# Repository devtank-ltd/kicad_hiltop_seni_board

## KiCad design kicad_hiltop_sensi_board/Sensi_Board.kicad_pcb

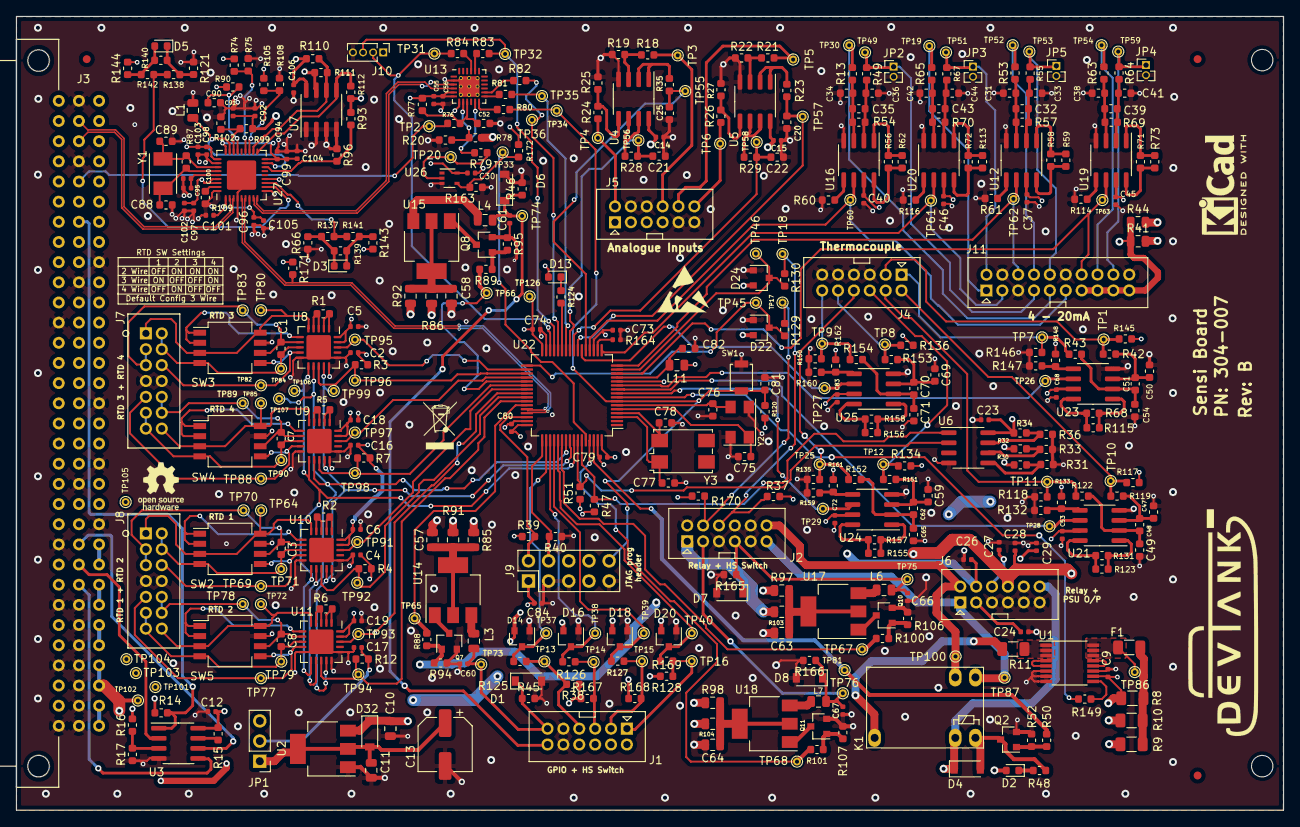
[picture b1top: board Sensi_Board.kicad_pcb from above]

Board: 4 copper layers, 159.6 x 100.0 mm, 451 parts (0 on the bottom side), 240 nets.

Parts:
C1, C3, C7, C8, C20, C21, C22, C25, C32, C35, C39, C43, C48, C51, C52, C62, C70, C81, C82, C90: 100nF; C_0603_1608Metric
C2, C4, C5, C6, C9, C12, C14, C15, C16, C17, C18, C19, C23, C24, C26, C27, C28, C29, C30, C37, C40, C45, C46, C53, C56, C60, C61, C66, C67, C68, C72, C73, C74, C79, C80, C83, C84, C92, C94, C95, C96, C97, C98, C99, C101: 100nF; C_0402_1005Metric
C10, C11: 10uF; C_0805_2012Metric
C13: 100uF; CP_Elec_6.3x7.7
C31, C33, C34, C36, C38, C41, C42, C44: 1uF; C_0603_1608Metric
C47, C49, C50, C54, C59, C65, C69, C71: 1nF; C_0603_1608Metric
C55, C100, C102, C103, C104, C105: 4.7uF; C_0402_1005Metric
C57, C58, C63, C64: DNF; C_0805_2012Metric
C75, C76: 18pF; C_0603_1608Metric
C77, C78: 4.3pF; C_0603_1608Metric
C88, C89: 33pF; C_0603_1608Metric
C91: 1uF; C_0402_1005Metric
C106: DNF; C_0402_1005Metric
D1, D6, D7, D8: D_Schottky; D_SOD-123
D2, D3, D5, D13: GRN; LED_0603_1608Metric
D4: BAT54T1G; D_SOD-123
D14, D16, D18, D20, D22, D24: BAV99; SOT-23
D32: MBR230LSFT1G; D_SOD-123
F1: Polyfuse; R_1206_3216Metric
J1, J2, J4, J5, J6: Conn_02x06_Top_Bottom; Molex2x06
J3: Conn_03x32_DIN41612; Socket_DIN41612-CaseC1-full-Male-96Pin-3rows_correct
J7, J8: Conn_02x07_Top_Bottom; 87831-1420_Molex_Milligrid
J9: Conn_02x05_Odd_Even; PinHeader_2x05_P2.54mm_Vertical
J10: Conn_01x04; PinHeader_1x04_P1.27mm_Vertical
J11: Conn_02x10_Counter_Clockwise; Molex_Milligrid_2x10
JP1: Jumper_NC_Dual; PinHeader_1x03_P2.54mm_Vertical
JP2, JP3, JP4, JP5: Jumper_NC_Small; PinHeader_1x02_P1.27mm_Vertical
K1: HRS1KH-S; Relay_SPDT_HRS1KH-S
L1: 500mA/0.10DCR; L_0805_2012Metric
L3, L4, L6, L7, L11: 2A/0.05DCR; L_0805_2012Metric
Q2, Q7, Q8, Q10, Q11: ZXMN6A07F; SOT-23
R1, R2, R5, R6, R50: 470R; R_0603_1608Metric
R3, R4, R7, R12, R14, R18, R21, R24, R26, R37, R52, R75, R77, R99, R105, R111, R120, R132, R133, R147, R148, R159, R160, R161, R162, R170: 10K; R_0603_1608Metric
R8, R9: DNF; R_1206_3216Metric
R10, R11: 0R; R_1206_3216Metric
R13, R49, R53, R55, R63, R64, R65, R67: 68R; R_0603_1608Metric
R15, R16, R47, R51: 4K7; R_0603_1608Metric
R17, R31, R33, R36, R38, R59, R62, R73, R74, R96, R108, R110, R112, R113, R115, R123, R137, R138, R143, R144, R155, R156, R163, R167, R168, R169, R172: DNF; R_0603_1608Metric
R19, R22, R25, R27: 16K; R_0603_1608Metric
R20: 47K; R_0603_1608Metric
R23, R28, R29, R35: 100R; R_0603_1608Metric
R30, R32, R34, R60, R61, R66, R76, R79, R80, R83, R84, R114, R116, R121, R149: 0R; R_0603_1608Metric
R39, R40, R45, R46, R90, R93, R94, R95, R106, R107, R139, R140, R165, R166: 100K; R_0603_1608Metric
R41, R85, R86, R97, R98: DNF; R_0805_2012Metric
R42, R43, R88, R89, R100, R101, R119, R122, R125, R126, R127, R128, R129, R130, R151, R152, R153, R154: 1K; R_0603_1608Metric
R44, R91, R92, R103, R104: 0R; R_0805_2012Metric
R48: 2K2; R_0603_1608Metric
R54, R57, R69, R70: 30R; R_0603_1608Metric
R56, R58, R71, R72: 12.4K; R_0603_1608Metric
R68, R131, R157, R158: 1.58K; R_0603_1608Metric
R78: 24K; R_0603_1608Metric
R81, R82, R124, R141, R142: 330R; R_0603_1608Metric
R87: 1M; R_0603_1608Metric
R102: 20K; R_0603_1608Metric
R109: 12.0K; R_0603_1608Metric
R117, R118, R134, R135, R136, R145, R146, R150: 10M; R_0603_1608Metric
R164: DNF; R_0402_1005Metric
R171: 1k5; R_0603_1608Metric
SW1: SW_Push; SW_SPST_B3U-1000P
SW2, SW3, SW4, SW5: SW_DIP_x04; SW_DIP_SPSTx04_Slide_Copal_CHS-04B_W7.62mm_P1.27mm
TP1, TP2, TP3, TP4, TP5, TP6, TP7, TP8, TP9, TP10, TP11, TP12, TP13, TP14, TP15, TP16, TP17, TP18, TP19, TP20, TP25, TP26, TP27, TP28, TP29, TP30, TP31, TP32, TP33, TP34, TP35, TP36, TP37, TP38, TP39, TP40, TP45, TP46, TP49, TP51, TP52, TP53, TP54, TP55, TP56, TP57, TP58, TP59, TP60, TP61, TP62, TP63, TP64, TP65, TP66, TP67, TP68, TP69, TP70, TP71, TP72, TP73, TP74, TP75, TP76, TP77, TP78, TP79, TP80, TP81, TP82, TP83, TP84, TP85, TP86, TP87, TP88, TP89, TP90, TP91, TP92, TP93, TP94, TP95, TP96, TP97, TP98, TP99, TP100, TP101, TP102, TP103, TP104, TP105, TP106, TP107, TP126: Test_Point; TestPoint_THTPad_D1.0mm_Drill0.5mm
U1: INA250A4; TSSOP-16_4.4x5mm_P0.65mm
U2: LD1117S33TR_SOT223; SOT-223-3_TabPin2
U3: AT25DN512CSSHF-B; SOIC-8_3.9x4.9mm_P1.27mm
U4, U5: AD8646; SOIC-8_3.9x4.9mm_P1.27mm
U6: LM75B; SOIC-8_3.9x4.9mm_P1.27mm
U7: DNF; SOIC-8_3.9x4.9mm_P1.27mm
U8, U9, U10, U11: MAX31865; TQFN-20-1EP_5x5mm_P0.65mm_EP3.1x3.1mm
U12, U16, U19, U20, U21, U23, U24, U25: MAX4194; SOIC-8_3.9x4.9mm_P1.27mm
U13: CP2102N-A01-GQFN24; CP2102_QFN-24-1EP_4x4mm_P0.5mm_EP2.6x2.6mm_ThermalVias_0.3m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
U14, U15, U17, U18: BTS4140N; SOT-223
U22: STM32F072RBTx; LQFP-64_10x10mm_P0.5mm
U26: M74VHC1GT14DFT2G; SOT-353_SC-70-5
U27: USB2502; QFN-36-1EP_6x6mm_P0.5mm_EP3.7x3.7mm
Y1: 50ppm 24.000MHZ; Crystal_SMD_TXC_7A-2Pin_5x3.2mm
Y2: 8MHZ; Crystal_SMD_Abracon_ABM3C-4Pin_5.0x3.2mm
Y3: ABS25-32.768KHZ-6-T; Crystal_SMD_7050-4Pin_7.0x5.0mm

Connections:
+3V3: C2.1, C4.1, C5.1, C6.1, C9.1, C12.2, C16.1, C17.1, C18.1, C19.1, C23.1, C27.1, C30.2, C37.2, C40.2, C45.2, C46.2, C53.2, C55.1, C56.1, C68.2, C72.2, C73.1, C74.1, C79.1, C80.1, C83.2, C84.2, C96.1, C97.1, C98.1, C101.1, C102.1, C103.1, C105.1, C106.1, D13.2, D14.2, D16.2, D18.2, D20.2, D22.2, D24.2, J6.9, J9.1, J10.1, JP1.2, L11.1, R3.1, R4.1, R7.1, R8.2, R12.1, R14.2, R15.2, R16.2, R30.1, R32.1, R34.1, R37.1, R38.1, R39.1, R47.1, R51.1, R74.1, R77.2, R90.1, R93.1, R105.2, R110.2, R112.1, R117.1, R120.1, R133.2, R134.1, R136.1, R143.2, R144.2, R145.1, R148.2, R161.2, R162.2, R167.1, R168.1, R169.1, R170.1, R171.1, R172.1, TP126.1, U1.10, U3.8, U6.8, U7.8, U8.19, U8.20, U9.19, U9.20, U10.19, U10.20, U11.19, U11.20, U12.7, U13.5, U13.6, U13.7, U16.7, U19.7, U20.7, U21.7, U22.19, U22.32, U22.48, U22.64, U23.7, U24.7, U25.7, U26.5, U27.1, U27.7, U27.13, U27.28, U27.33, U27.34
+3V3_BP: J3.7c, J3.8c, JP1.3, TP104.1
+3V3_LOC: C11.2, C13.1, D32.2, JP1.1, U2.2
+5V: C10.2, C14.2, C15.2, C29.1, C91.1, C92.1, D2.2, D4.1, D32.1, J3.3c, J3.4c, J5.1, J5.2, J5.3, J5.4, J6.12, K1.5, R78.2, R99.1, TP102.1, U2.3, U4.8, U5.8
+12V: C28.1, J3.1c, J3.2c, J6.10, R10.2, R41.2, R85.1, R86.1, R97.1, R98.1, TP101.1
-5V: C26.1, J3.5c, J3.6c, J6.8, TP103.1
/AIN_BUF_CH1: C25.2, R35.1, TP55.1, U22.21
/AIN_BUF_CH2: C21.2, R28.1, TP56.1, U22.25
/AIN_BUF_CH3: C20.2, R23.1, TP57.1, U22.23
/AIN_BUF_CH4: C22.2, R29.1, TP58.1, U22.24
/AIN_CH1: J5.10, R18.2, TP3.1
/AIN_CH2: J5.7, R24.2, TP4.1
/AIN_CH3: J5.11, R21.2, TP5.1
/AIN_CH4: J5.12, R26.2, TP6.1
/F1+: J11.5, R13.2, TP30.1
/F1-: J11.4, JP2.1, R49.2, TP49.1
/F1_OUT: J11.6, TP60.1, U16.6, U22.20
/F2+: J11.1, R65.2, TP19.1
/F2-: J11.11, JP3.1, R67.2, TP51.1
/F2_OUT: J11.2, TP61.1, U20.6, U22.17
/F3+: J11.14, R53.2, TP52.1
/F3-: J11.15, JP5.1, R55.2, TP53.1
/F3_OUT: J11.13, TP62.1, U12.6, U22.16
/F4+: J11.18, R63.2, TP54.1
/F4-: J11.19, JP4.1, R64.2, TP59.1
/F4_OUT: J11.17, TP63.1, U19.6, U22.14
/F_Vs: J11.7, J11.8, J11.9, J11.10, R41.1, R44.1
/GPIO1: D14.3, R125.1, TP37.1, U22.50
/GPIO1_EXT: J1.4, R38.2, R125.2, TP13.1
/GPIO2: D16.3, R126.1, TP38.1, U22.51
/GPIO2_EXT: J1.3, R126.2, R167.2, TP14.1
/GPIO3: D18.3, R127.1, TP39.1, U22.52
/GPIO3_EXT: J1.2, R127.2, R168.2, TP15.1
/GPIO4: D20.3, R128.1, TP40.1, U22.53
/GPIO4_EXT: J1.1, R128.2, R169.2, TP16.1
/GPIO5: D22.3, R129.1, TP45.1, U22.33
/GPIO5_EXT: J2.8, R129.2, R170.2, TP17.1
/GPIO6: D24.3, R130.1, TP46.1, U22.15
/GPIO6_EXT: J2.9, R37.2, R130.2, TP18.1
/HS_CTRL_SW1: R88.2, TP65.1, U22.43
/HS_CTRL_SW2: R89.2, TP66.1, U22.37
/HS_CTRL_SW3: R100.2, TP67.1, U22.54
/HS_CTRL_SW4: R101.2, TP68.1, U22.61
/HS_OUT1: C60.1, D1.1, J1.6, L3.1, R45.1, TP73.1
/HS_OUT2: C61.1, D6.1, J1.12, L4.1, R46.1, TP74.1
/HS_OUT3: C66.1, D7.1, J2.4, L6.1, R165.1, TP75.1
/HS_OUT4: C67.1, D8.1, J2.2, L7.1, R166.1, TP76.1
/I_MON: R149.2, U1.9
/OUT1_COM: K1.2, R11.1
/OUT1_NC: J2.6, J6.1, K1.4, TP87.1
/OUT1_NO: J2.12, J6.7, K1.3, TP100.1
/PORT_SEL: J3.26b, R14.1, U3.1
/RESET: J3.28b, R76.2, TP2.1
/RL1_OUT: R50.2, TP81.1, U22.62
/RTD1_CS: R4.2, TP92.1, U10.13, U22.41
/RTD1_F+: J8.1, SW2.3, SW2.8, TP64.1, U10.5
/RTD1_F-: J8.10, SW2.5, TP69.1, U10.9
/RTD1_INT: TP91.1, U10.18, U22.39
/RTD1_R+: C3.2, J8.2, J8.3, SW2.6, TP70.1, U10.7
/RTD1_R-: C3.1, J8.8, J8.9, SW2.4, TP71.1, U10.8
/RTD2_CS: R12.2, TP94.1, U11.13, U22.42
/RTD2_F+: J8.14, SW5.3, SW5.8, TP72.1, U11.5
/RTD2_F-: J8.5, SW5.5, TP77.1, U11.9
/RTD2_INT: TP93.1, U11.18, U22.40
/RTD2_R+: C8.2, J8.12, J8.13, SW5.6, TP78.1, U11.7
/RTD2_R-: C8.1, J8.6, J8.7, SW5.4, TP79.1, U11.8
/RTD3_CS: R3.2, TP96.1, U8.13, U22.35
/RTD3_F+: J7.1, SW3.3, SW3.8, TP80.1, U8.5
/RTD3_F-: J7.10, SW3.5, TP82.1, U8.9
/RTD3_INT: TP95.1, U8.18, U22.34
/RTD3_R+: C1.2, J7.2, J7.3, SW3.6, TP83.1, U8.7
/RTD3_R-: C1.1, J7.8, J7.9, SW3.4, TP84.1, U8.8
/RTD4_CS: R7.2, TP98.1, U9.13, U22.38
/RTD4_F+: J7.14, SW4.3, SW4.8, TP85.1, U9.5
/RTD4_F-: J7.5, SW4.5, TP88.1, U9.9
/RTD4_INT: TP97.1, U9.18, U22.36
/RTD4_R+: C7.2, J7.12, J7.13, SW4.6, TP89.1, U9.7
/RTD4_R-: C7.1, J7.6, J7.7, SW4.4, TP90.1, U9.8
/SPI0_CLK: J3.10b, U3.6
/SPI0_MISO: J3.9b, U3.2
/SPI0_MOSI: J3.8b, U3.5
/STM_BOOT0_OUT: R163.1, R172.2, TP33.1, U22.60, U26.4
/STM_DEBUG_RX: J10.2, R84.1, TP31.1, U22.30
/STM_DEBUG_TX: J10.3, R83.1, TP32.1, U22.29
/STM_Micro/ADC8: R149.1, U22.8
/STM_RES1: R81.1, TP35.1, U22.26
/STM_RES2: R82.1, TP36.1, U22.28
/STM_RESET: C81.1, J9.10, R80.1, R120.2, SW1.2, TP34.1, U22.7
/STM_SCL: R51.2, U6.2, U22.58
/STM_SDA: R47.2, U6.1, U22.59
/STM_SPI1_MISO: TP99.1, U8.14, U9.14, U10.14, U11.14, U22.56
/STM_SPI1_MOSI: TP106.1, U8.11, U9.11, U10.11, U11.11, U22.57
/STM_SPI1_SCK: TP107.1, U8.12, U9.12, U10.12, U11.12, U22.55
/STM_USB_DATA_N: U22.44, U27.5
/STM_USB_DATA_P: R171.2, U22.45, U27.6
/SWD_IO: J9.2, R39.2, U22.46
/SWD_SCK: J9.4, R40.2, U22.49
/TH1+: J4.2, R42.2, R145.2, TP1.1
/TH1-: J4.1, R43.2, R146.1, TP7.1
/TH1_OUT: TP26.1, U22.11, U23.6
/TH2+: J4.11, R136.2, R153.2, TP8.1
/TH2-: J4.12, R150.1, R154.2, TP9.1
/TH2_OUT: TP27.1, U22.22, U25.6
/TH3+: J4.7, R117.2, R119.2, TP10.1
/TH3-: J4.8, R118.1, R122.2, TP11.1
/TH3_OUT: TP28.1, U21.6, U22.10
/TH4+: J4.9, R134.2, R151.2, TP12.1
/TH4-: J4.10, R135.1, R152.2, TP25.1
/TH4_OUT: TP29.1, U22.9, U24.6
/USB_DATA_N: J3.30b, U27.3
/USB_DATA_P: J3.31b, U27.2
/USB_DEBUG_N: U13.4, U27.9
/USB_DEBUG_P: U13.3, U27.8
ADJ_DC: C24.1, J2.1, J3.9c, J3.10c, J6.2, R9.2, R44.2, R91.1, R92.1, R103.1, R104.1, TP105.1
GND: C2.2, C4.2, C5.2, C6.2, C9.2, C10.1, C11.1, C12.1, C13.2, C14.1, C15.1, C16.2, C17.2, C18.2, C19.2, C20.1, C21.1, C22.1, C23.2, C24.2, C25.1, C26.2, C27.2, C28.2, C29.2, C30.1, C31.1, C33.2, C34.1, C36.2, C37.1, C38.1, C40.1, C41.2, C42.1, C44.2, C45.1, C46.1, C47.1, C49.2, C50.1, C52.2, C53.1, C54.2, C55.2, C56.2, C57.2, C58.2, C59.1, C60.2, C61.2, C63.2, C64.2, C65.2, C66.2, C67.2, C68.1, C69.1, C71.2, C72.1, C73.2, C74.2, C75.2, C76.2, C77.2, C78.2, C79.2, C80.2, C81.2, C82.2, C83.1, C84.1, C88.2, C89.1, C90.2, C91.2, C92.2, C94.2, C95.2, C96.2, C97.2, C98.2, C99.2, C100.2, C101.2, C102.2, C103.2, C104.2, C105.2, C106.2, D1.2, D6.2, D7.2, D8.2, D14.1, D16.1, D18.1, D20.1, D22.1, D24.1, J1.5, J1.11, J2.3, J2.5, J2.7, J2.10, J2.11, J3.1a, J3.1b, J3.2b, J3.3b, J3.4a, J3.4b, J3.5b, J3.6b, J3.7a, J3.7b, J3.10a, J3.11c, J3.13b, J3.14c, J3.17c, J3.21a, J3.23b, J3.24c, J3.29b, J3.32b, J4.3, J4.4, J4.5, J4.6, J5.5, J5.6, J5.8, J5.9, J6.3, J6.4, J6.5, J6.6, J6.11, J7.4, J7.11, J8.4, J8.11, J9.3, J9.5, J9.9, J10.4, J11.3, J11.12, J11.16, J11.20, JP2.2, JP3.2, JP4.2, JP5.2, L1.1, Q2.2, Q7.2, Q8.2, Q10.2, Q11.2, R17.1, R19.1, R20.1, R22.1, R25.1, R27.1, R31.2, R33.2, R36.2, R40.1, R45.2, R46.2, R52.1, R60.2, R61.2, R66.1, R75.1, R94.1, R95.1, R96.1, R102.2, R106.1, R107.1, R108.2, R109.2, R111.2, R114.2, R116.2, R118.2, R121.1, R132.2, R135.2, R146.2, R147.2, R150.2, R159.2, R160.2, R163.2, R164.2, R165.2, R166.2, SW1.1, SW2.7, SW3.7, SW4.7, SW5.7, U1.6, U1.7, U1.8, U1.11, U2.1, U3.4, U4.4, U5.4, U6.4, U7.1, U7.2, U7.3, U7.4, U7.7, U8.10, U8.15, U8.16, U8.21, U9.10, U9.15, U9.16, U9.21, U10.10, U10.15, U10.16, U10.21, U11.10, U11.15, U11.16, U11.21, U12.4, U13.2, U13.25, U16.4, U19.4, U20.4, U21.4, U22.12, U22.31, U22.47, U22.63, U23.4, U24.4, U25.4, U26.3, U27.4, U27.10, U27.29, U27.36, U27.37, Y2.2, Y2.4
unnamed: C31.2, C32.1, R53.1, R57.1, U12.3
unnamed: C32.2, C33.1, R55.1, R57.2, U12.2
unnamed: C34.2, C35.1, R13.1, R54.1, U16.3
unnamed: C35.2, C36.1, R49.1, R54.2, U16.2
unnamed: C38.2, C39.1, R63.1, R69.1, U19.3
unnamed: C39.2, C41.1, R64.1, R69.2, U19.2
unnamed: C42.2, C43.1, R65.1, R70.1, U20.3
unnamed: C43.2, C44.1, R67.1, R70.2, U20.2
unnamed: C47.2, C48.1, R119.1, U21.3
unnamed: C48.2, C49.1, R122.1, U21.2
unnamed: C50.2, C51.1, R42.1, U23.3
unnamed: C51.2, C54.1, R43.1, U23.2
unnamed: C52.1, R76.1, R77.1, U13.9
unnamed: C57.1, R85.2, R91.2, U14.2, U14.4
unnamed: C58.1, R86.2, R92.2, U15.2, U15.4
unnamed: C59.2, C62.1, R151.1, U24.3
unnamed: C62.2, C65.1, R152.1, U24.2
unnamed: C63.1, R97.2, R103.2, U17.2, U17.4
unnamed: C64.1, R98.2, R104.2, U18.2, U18.4
unnamed: C69.2, C70.1, R153.1, U25.3
unnamed: C70.2, C71.1, R154.1, U25.2
unnamed: C75.1, U22.5, Y2.1
unnamed: C76.1, U22.6, Y2.3
unnamed: C77.1, U22.3, Y3.1
unnamed: C78.1, U22.4, Y3.4
unnamed: C82.1, L11.2, U22.13
unnamed: C88.1, R87.1, U27.31, Y1.2
unnamed: C89.2, R87.2, U27.30, Y1.1
unnamed: C90.1, R90.2, U27.24
unnamed: C95.1, C100.1, U27.32
unnamed: C94.1, C99.1, C104.1, U27.18, U27.27
unnamed: D2.1, R48.2
unnamed: D3.1, R66.2, R137.1, R139.1
unnamed: D3.2, R139.2, R141.2, R143.1
unnamed: D4.2, K1.1, Q2.3, R48.1
unnamed: D5.1, R121.2, R138.1, R140.1
unnamed: D5.2, R140.2, R142.2, R144.1
unnamed: D13.1, R124.1
unnamed: F1.1, TP86.1, U1.14, U1.15, U1.16
unnamed: F1.2, R8.1, R9.1, R10.1
unnamed: L1.2, U27.17, U27.26
unnamed: L3.2, U14.3
unnamed: L4.2, U15.3
unnamed: L6.2, U17.3
unnamed: L7.2, U18.3
unnamed: Q2.1, R50.1, R52.2
unnamed: Q7.1, R88.1, R94.2
unnamed: Q7.3, U14.1
unnamed: Q8.1, R89.1, R95.2
unnamed: Q8.3, U15.1
unnamed: Q10.1, R100.1, R106.2
unnamed: Q10.3, U17.1
unnamed: Q11.1, R101.1, R107.2
unnamed: Q11.3, U18.1
unnamed: R1.1, U8.1, U8.2
unnamed: R1.2, U8.3, U8.4
unnamed: R2.1, U10.1, U10.2
unnamed: R2.2, U10.3, U10.4
unnamed: R5.1, U9.1, U9.2
unnamed: R5.2, U9.3, U9.4
unnamed: R6.1, U11.1, U11.2
unnamed: R6.2, U11.3, U11.4
unnamed: R11.2, U1.1, U1.2, U1.3
unnamed: R15.1, U3.7
unnamed: R16.1, R17.2, U3.3
unnamed: R18.1, R19.2, U4.3
unnamed: R20.2, R78.1, U13.8
unnamed: R21.1, R22.2, U5.3
unnamed: R23.2, U5.1, U5.2
unnamed: R24.1, R25.2, U4.5
unnamed: R26.1, R27.2, U5.5
unnamed: R28.2, U4.6, U4.7
unnamed: R29.2, U5.6, U5.7
unnamed: R30.2, R31.1, U6.5
unnamed: R32.2, R33.1, U6.6
unnamed: R34.2, R36.1, U6.7
unnamed: R35.2, U4.1, U4.2
unnamed: R56.1, R62.1, U16.1
unnamed: R56.2, R62.2, U16.8
unnamed: R58.1, R59.1, U12.1
unnamed: R58.2, R59.2, U12.8
unnamed: R60.1, U16.5
unnamed: R61.1, U12.5
unnamed: R71.1, R73.1, U19.1
unnamed: R71.2, R73.2, U19.8
unnamed: R74.2, R75.2, U27.22
unnamed: R79.1, TP20.1, U26.2
unnamed: R79.2, U13.11
unnamed: R80.2, U13.12
unnamed: R81.2, U13.13
unnamed: R82.2, U13.14
unnamed: R83.2, U13.20
unnamed: R84.2, U13.21
unnamed: R93.2, R96.2, U27.16
unnamed: R99.2, R102.1, U27.25
unnamed: R105.1, R108.1, U27.21
unnamed: R109.1, U27.35
unnamed: R110.1, R111.1, U7.6, U27.20
unnamed: R112.2, U7.5, U27.19
unnamed: R72.1, R113.1, U20.1
unnamed: R72.2, R113.2, U20.8
unnamed: R114.1, U19.5
unnamed: R68.1, R115.1, U23.1
unnamed: R68.2, R115.2, U23.8
unnamed: R116.1, U20.5
unnamed: R123.1, R131.1, U21.1
unnamed: R123.2, R131.2, U21.8
unnamed: R124.2, U22.27
unnamed: R132.1, R133.1, U21.5
unnamed: R137.2, R141.1, U27.12
unnamed: R138.2, R142.1, U27.11
unnamed: R147.1, R148.1, U23.5
unnamed: R155.1, R157.1, U24.1
unnamed: R155.2, R157.2, U24.8
unnamed: R156.1, R158.1, U25.1
unnamed: R156.2, R158.2, U25.8
unnamed: R159.1, R161.1, U24.5
unnamed: R160.1, R162.1, U25.5
unnamed: R164.1, U22.18
unnamed: SW2.1, SW2.2, U10.6
unnamed: SW3.1, SW3.2, U8.6
unnamed: SW4.1, SW4.2, U9.6
unnamed: SW5.1, SW5.2, U11.6
unnamed: U1.4, U1.5
unnamed: U1.12, U1.13

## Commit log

2019-06-06 Setup base project for sensi board
2019-08-27 saved minor changes
2019-08-27 added project files
2019-08-28 Just about to aad the RTD
2019-08-28 added RTD sheet
2019-09-04 updated sensi board for LBBC 04/09/19
2019-09-04 updated sensi board for LBBC
2019-09-05 LBBC sensi board upto date schematic and footprints
2019-09-11 All sensors connected to STM Microcontroller
2019-09-11 Change common to be submodule as it should be.
2019-09-11 Add missing gitignore file.
2019-09-12 LBBC sensi board updated STM ADC pins, connectors added and most errors removed
2019-09-13 Updated LBBC board and Board layout started
2019-09-17 Started on Sensi Board Layout
2019-09-19 Updated board layout LBBC sensi board
2019-09-20 Updated sensi board layout LBBC
2019-09-20 Sensi board updated pin map
2019-09-25 Updated sensi board pin map and layout before PCB tracking
2019-09-26 Started PCB routing of Sensi Board LBBC
2019-09-26 Routing complete around the chip of sensi board
2019-09-26 Most of the routing of the sensi board complete
2019-10-01 Most major connections complete and differential tracking done on the Sensi board layout
2019-10-02 Most routing on Sensi Board complete
2019-10-02 Take latest common for new Molex connector.
2019-10-02 Pre stitching via for sensi board.
2019-10-07 Sensi board with references visible and without stitching vias
2019-10-08 Sensi board complete waiting for review
2019-10-15 Changes to Sensi board after review
2019-10-16 Sensi board schematic updated from comments
2019-10-23 Updated sensi board layout
2019-10-23 Sensi board layout awaiting review
2019-10-23 Missing connection added to Sensi Board
2019-10-25 Sensi Board Complete
2019-10-25 Sensi Board updated RTD table
2019-10-25 Sensi board keeport for u1
2019-10-25 Sensi board u1 filled in areas added
2019-10-29 Rev A ordered
2019-10-29 Take new common with molex and through hole changes.
2019-11-07 Pressure sensor calcs added to 4-20mA circuit
2021-02-04 starting revB
2021-02-09 revb design updated schematics and layout
2021-02-09 revB ready for review
2021-02-10 Sensi Board RevB
2021-02-10 updated footprints to simplify bom
2021-02-11 fiducials added to pcb
2021-02-11 cern license added to PCB
2022-10-13 bom added
2022-10-13 Update gitignore for new KiCAD's backups.

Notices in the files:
kicad_hiltop_sensi_board/Sensi_Board.kicad_pcb:
(c) Copyright 2021 Devtank Ltd
Licensed under CERN-OHL-W V2.0
https://cern-ohl.web.cern.ch
parts and their libraries:
Copyright 2016 Accelerated Designs. All rights reserved.
